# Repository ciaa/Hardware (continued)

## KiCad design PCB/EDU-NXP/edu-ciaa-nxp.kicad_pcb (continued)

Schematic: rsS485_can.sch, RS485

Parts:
C1: 10uF; c_1206_tantalio; Digikey 399-3525-1-ND
C2: 100nF; c_0805; Digikey 399-1167-1-ND
D1, D2, D3: PSD12C; DO-214AA(SMB); Digikey P6SMB12CAT3GOSCT-ND
J1: TB_1X3; bornier3; Digikey ED2610-ND
JP1, JP2, JP3, JP4: JUMPER-2
PS1, PS2: USMF020; SM1210; Digikey MF-USMF020-2CT-ND
R1, R2, R3: 4K7; SM0805; Digikey 1276-5544-1-ND
R4, R5: 100K; SM0805; Digikey P100KACT-ND
R6, R8: 390; SM0805; Digikey RR12P390DCT-ND
R7: 200; SM0805; Digikey RR12P200DCT-ND
R9: 100; SM0805; Digikey P16057CT-ND
U1: SN65HVD1176DR; -SOIC8; Digikey 296-26337-1-ND

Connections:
+5V: C1.2, C2.1 (A), R4.1 (A), R6.1 (A), U1.8 (VCC); also elsewhere on the board
/CPU/RS485_DIR: JP1.1, R3.1 (A), U1.3 (DE); also elsewhere on the board
/CPU/RS485_RXD: R1.2 (B), U1.1 (RO); also elsewhere on the board
/CPU/RS485_TXD: U1.4 (DI); also elsewhere on the board
GND: C1.1 (GND), C2.2 (B), D1.1 (cathode), D3.2 (Anode), R2.2 (B), R3.2 (B), R5.2 (B), R8.2 (B), R9.1 (A), U1.5 (GND); also elsewhere on the board
unnamed: J1.3, R9.2 (B)
unnamed: JP4.1, R8.1 (A)
unnamed: JP3.1, R7.1 (A)
unnamed: J1.2, PS2.2
unnamed: J1.1, PS1.2
unnamed: JP2.2, R6.2 (B)
unnamed: JP1.2, R2.1 (A), U1.2 (~RE~)
unnamed: D1.2 (Anode), D2.1 (cathode), JP2.1, JP3.2, PS1.1, R4.2 (B), U1.6 (A)
unnamed: D2.2 (Anode), D3.1 (cathode), JP4.2, PS2.1, R5.1 (A), R7.2 (B), U1.7 (B)

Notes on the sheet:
RS485
JP2, JP3, JP4: cortocircuitar en caso que sea el último nodo de la red.
Los resistores de 290 y 200 (220 valor E12/E24) se denominas bias resistors y son los recomendados la especificación de Profibus.
R9 de acuerdo a Fig 27 de la AN: slla070d de TI.

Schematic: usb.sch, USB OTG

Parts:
C3: 10uF; c_1206_tantalio; Digikey 399-3525-1-ND
C4, C50: 100nF; c_0805; Digikey 399-1167-1-ND
FB1: MI0805M221R-10; SM0805; Digikey 240-2392-1-ND
FB2: HZ0805E601R-10; SM0805; Digikey 240-2399-1-ND
J2: ZX62D-AB-5P8; USB_microAB_ZX62-AB-5P8; Digikey H11494CT-ND
R16, R17: 10k; SM0805; Digikey P10KACT-ND
TR1: DLW21HN900SQ2; SRF2012; Digikey 490-1064-2-ND
U2: PRTR5V0U2X; sot143B; Digikey 568-4140-1-ND
U9: MIC2025; -SOIC8; Digikey 576-1058-ND

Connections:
+5V: C50.1, U9.7; also elsewhere on the board
/CPU/USB_DM: TR1.3, U2.2 (I/O); also elsewhere on the board
/CPU/USB_DP: TR1.2, U2.3 (I/O); also elsewhere on the board
/CPU/USB_ID: J2.4; also elsewhere on the board
/CPU/USB_PPWR: R17.2, U9.1; also elsewhere on the board
/CPU/USB_PWR_FAULT: R16.1, U9.2; also elsewhere on the board
/CPU/USB_VBUS: C3.1, C4.1, FB1.2, U2.4 (VCC), U9.6, U9.8; also elsewhere on the board
/USB_OTG/CHJ2: FB2.2, J2.6, J2.7, J2.8, J2.9, U2.1 (GND)
GND: C3.2, C4.2, C50.2, FB2.1, J2.5, R17.1, U9.3; also elsewhere on the board
unnamed: FB1.1, J2.1
unnamed: J2.2, TR1.4
unnamed: J2.3, TR1.1

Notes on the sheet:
USB OTG
POWER SWITCH
ESD PROTECTION
Par diferencial 90 Ohm

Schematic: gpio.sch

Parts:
P1, P2: CONN_20X2
R20: 470; SM0805; Digikey P470ACT-ND
R21, R22, R23: 1k2; SM0805; Digikey RMCF0805JT1K20CT-ND
TH1, TH2, TH3, TH4: MF-MSMF030-2; MF-MSMF; Digikey MF-MSMF030-2CT-ND

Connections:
+3.3VADC: P1.17; also elsewhere on the board
+5V: TH2.2, TH4.2; also elsewhere on the board
/CPU/ADC0_1: R21.1; also elsewhere on the board
/CPU/ADC0_2: R22.1; also elsewhere on the board
/CPU/ADC0_3: R23.1; also elsewhere on the board
/CPU/CAN_RD: P1.27; also elsewhere on the board
/CPU/CAN_TD: P1.29; also elsewhere on the board
/CPU/DAC: R20.1; also elsewhere on the board
/CPU/ENET_CRS_DV: P2.10; also elsewhere on the board
/CPU/ENET_MDC: P2.8; also elsewhere on the board
/CPU/ENET_MDIO: P2.12; also elsewhere on the board
/CPU/ENET_REF_CLK: P2.15; also elsewhere on the board
/CPU/ENET_RXD0: P2.9; also elsewhere on the board
/CPU/ENET_RXD1: P2.4; also elsewhere on the board
/CPU/ENET_TXD0: P2.14; also elsewhere on the board
/CPU/ENET_TXD1: P2.16; also elsewhere on the board
/CPU/ENET_TX_EN: P2.6; also elsewhere on the board
/CPU/GPIO0: P2.29; also elsewhere on the board
/CPU/GPIO1: P2.32; also elsewhere on the board
/CPU/GPIO2: P2.31; also elsewhere on the board
/CPU/GPIO3: P2.34; also elsewhere on the board
/CPU/GPIO4: P2.33; also elsewhere on the board
/CPU/GPIO5: P2.36; also elsewhere on the board
/CPU/GPIO6: P2.35; also elsewhere on the board
/CPU/GPIO7: P2.38; also elsewhere on the board
/CPU/GPIO8: P2.40; also elsewhere on the board
/CPU/I2C_SCL: P1.21; also elsewhere on the board
/CPU/I2C_SDA: P1.19; also elsewhere on the board
/CPU/ISP: P1.5; also elsewhere on the board
/CPU/LCD1: P2.30; also elsewhere on the board
/CPU/LCD2: P2.28; also elsewhere on the board
/CPU/LCD3: P2.26; also elsewhere on the board
/CPU/LCD4: P2.22; also elsewhere on the board
/CPU/LCD_RS: P2.24; also elsewhere on the board
/CPU/RESET: P1.3; also elsewhere on the board
/CPU/RS232_RXD: P1.23; also elsewhere on the board
/CPU/RS232_TXD: P1.25; also elsewhere on the board
/CPU/SPI_MISO: P2.18; also elsewhere on the board
/CPU/SPI_MOSI: P2.21; also elsewhere on the board
/CPU/SPI_SCK: P2.20; also elsewhere on the board
/CPU/TEC_COL0: P1.39; also elsewhere on the board
/CPU/TEC_COL1: P1.31; also elsewhere on the board
/CPU/TEC_COL2: P1.34; also elsewhere on the board
/CPU/TEC_F0: P1.33; also elsewhere on the board
/CPU/TEC_F1: P1.36; also elsewhere on the board
/CPU/TEC_F2: P1.37; also elsewhere on the board
/CPU/TEC_F3: P1.35; also elsewhere on the board
/GPIO/LCD_EN: P2.23; also elsewhere on the board
/GPIO/WAKEUP: P1.6; also elsewhere on the board
GND: P1.4, P1.20, P1.22, P1.24, P1.26, P1.28, P1.30, P1.32, P1.38, P1.40, P2.3, P2.5, P2.7, P2.11, P2.13, P2.17, P2.19, P2.25, P2.27, P2.37, P2.39; also elsewhere on the board
GNDA: P1.7, P1.8, P1.10, P1.12, P1.14, P1.16, P1.18; also elsewhere on the board
unnamed: P1.1, TH1.1
unnamed: P1.2, TH2.1
unnamed: P1.15, R20.2
unnamed: P1.13, R21.2
unnamed: P1.11, R22.2
unnamed: P1.9, R23.2
unnamed: P2.2, TH4.1
unnamed: P2.1, TH3.1

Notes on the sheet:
Conectores de expansión LVTTL. En formato de pines, 2.54mm de pitch.
GPIO

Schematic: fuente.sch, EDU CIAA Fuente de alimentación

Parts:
C5, C6: 10uF; c_1206_tantalio; Digikey 399-3684-2-ND
C49: 100nF; c_0805; Digikey 399-1167-1-ND
D4, D5, D10: PMEG3020EH; DO-214AA(SMB); Digikey 568-4129-1-ND
D6: LED red; LED-0805; Digikey 1080-1412-1-ND
FB3, FB4: HZ0805E601R-10; SM0805; Digikey 240-2399-1-ND
P4: WM4200-ND; Con_2P; Digikey WM4200-ND
R57: 1k; SM0805; Digikey 311-1.0KARCT-ND
U3: NCP1117ST33T3G; SOT223; Digikey NCP1117ST33T3GOSCT-ND
ZA1: SMAZ5V6; SOD123F; Digikey MMSZ5V6T1GOSCT-ND

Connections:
+3.3VADC: FB3.2; also elsewhere on the board
+5V: C5.1, C49.1, D4.2 (K), D5.2 (K), D10.2 (K), R57.1, U3.3 (VI), ZA1.2 (K); also elsewhere on the board
/CPU/USB_DEBUG_VBUS: D5.1 (A); also elsewhere on the board
/CPU/USB_VBUS: D4.1 (A); also elsewhere on the board
GND: C5.2, C6.2, C49.2, D6.2 (K), FB4.1, P4.1, U3.1 (GND), ZA1.1 (A); also elsewhere on the board
GNDA: FB4.2; also elsewhere on the board
unnamed: D10.1 (A), P4.2
unnamed: D6.1 (A), R57.2

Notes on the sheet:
Fuente de alimentación a través de los puertos USB o de la entrada de 5V Tensiones de salida: 5V y 3.3V

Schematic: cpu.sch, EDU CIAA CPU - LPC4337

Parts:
BT1: BK-913; BK-913-ND; Digikey BK-913-ND
C11, C12, C13, C14, C15, C16: 20p; c_0805; Digikey 399-8033-1-ND
C17, C18, C19, C20, C21, C22, C23, C24, C25, C26, C27, C28, C29, C30, C31, C32, C34, C36, C38, C40, C41, C42, C43, C44, C45, C46, C47, C48, C51: 100nF; c_0805; Digikey 399-1167-1-ND
C33, C37, C39: 10uF; c_1206_tantalio; Digikey 399-3525-1-ND
C35: 3.3uF; c_0805; Digikey 445-7582-1-ND
D11: LL4148; SOD-80; Digikey LL4148FSTR-ND
FB5, FB6, FB9, FB10: MI0805M221R-10; SM0805; Digikey 240-2392-1-ND
FB7, FB8: HZ0805E601R-10; SM0805; Digikey 240-2399-1-ND
J3: ZX62D-AB-5P8; USB_microAB_ZX62-AB-5P8; Digikey H11494CT-ND
JP5: ISP
P3: Cortex-Debug; Pin_Array_5x2_1.27mm_SMD; Digikey FTSH-105-01-L-DV-K-TR-ND
R11, R15, R107, R108, R109, R110: 0; SM0805; Digikey 311-0.0ARCT-ND
R90: 100K; SM0805; Digikey P100KACT-ND
R91: 10M; SM0805; Digikey RMCF0805JT10M0CT-ND
R92: 12K; SM0805; Digikey 311-12.0KCRCT-ND
R93, R94, R99, R100, R102: 10K; SM0805; Digikey P10KACT-ND
R95, R97: 2.2k; SM0805; Digikey RMCF0805JT2K20CT-ND
R96, R98: 15K; SM0805; Digikey RR12P15.0KDCT-ND
R101: 2.2K; SM0805; Digikey RMCF0805JT2K20CT-ND
R103: 12K 1%; SM0805; Digikey 311-12.0KCRCT-ND
R104: 1k; SM0805; Digikey RR12P15.0KDCT-ND
R105: 270; SM0805; Digikey RHM270CPCT-ND
R106: 10k; SM0805; Digikey P10KACT-ND
SW5: RESET; PUSH_SWITCH_THT; Digikey 450-1804-ND
TR2: DLW21HN900SQ2; SRF2012; Digikey 490-1064-2-ND
U4: LPC4337JBD144; LQFP144-M05; Digikey 568-10159-ND
U5: 93C46; -SOIC8; Digikey AT93C46DN-SH-TCT-ND
U6: FT2232H; LQFP64-M05; Digikey 768-1024-1-ND
U7: TXB0108; tssop-20; Digikey 296-21527-1-ND
U8: PRTR5V0U2X; sot143B; Digikey 568-4140-1-ND
X1: 32.768K; 4SOJ; Digikey 535-9166-1-ND
X2, X3: 12MHz; FA238V-XTAL; Digikey 887-1831-1-ND

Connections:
+3.3VADC: C18.1, C19.1, C32.1, C33.2, FB10.2, U4.137 (VDDA); also elsewhere on the board
/CPU/ADC0_1: U4.2 (ADC0_1/ADC1_1); also elsewhere on the board
/CPU/ADC0_2: U4.143 (ADC0_2/ADC1_2); also elsewhere on the board
/CPU/ADC0_3: U4.139 (ADC0_3/ADC1_3); also elsewhere on the board
/CPU/CAN_RD: U4.114 (P3_1); also elsewhere on the board
/CPU/CAN_TD: U4.116 (P3_2); also elsewhere on the board
/CPU/CHJ3: FB5.1, J3.6, J3.7, J3.8, J3.9, U8.1 (GND)
/CPU/DAC: U4.6 (ADC0_0/ADC1_0/DAC); also elsewhere on the board
/CPU/EECLK: R100.2, U5.2 (SK), U6.62 (EECLK)
/CPU/EECS: R102.2, U5.1 (CS), U6.63 (EECS)
/CPU/EEDATA: R101.1, U5.3 (DI), U6.61 (EEDATA)
/CPU/ENET_CRS_DV: U4.64 (P1_16); also elsewhere on the board
/CPU/ENET_MDC: U4.140 (P7_7); also elsewhere on the board
/CPU/ENET_MDIO: U4.66 (P1_17); also elsewhere on the board
/CPU/ENET_REF_CLK: U4.68 (P1_19); also elsewhere on the board
/CPU/ENET_RXD0: U4.62 (P1_15); also elsewhere on the board
/CPU/ENET_RXD1: U4.32 (P0_0); also elsewhere on the board
/CPU/ENET_TXD0: U4.67 (P1_18); also elsewhere on the board
/CPU/ENET_TXD1: U4.70 (P1_20); also elsewhere on the board
/CPU/ENET_TX_EN: U4.34 (P0_1); also elsewhere on the board
/CPU/FT_OE: R105.2, U6.28 (ACBUS2)
/CPU/FT_RST: U6.27 (ACBUS1), U7.7 (A6)
/CPU/FT_TCK: U6.16 (ADBUS0), U7.1 (A1)
/CPU/FT_TDI: U6.17 (ADBUS1), U7.3 (A2)
/CPU/FT_TDO: U6.18 (ADBUS2), U7.4 (A3)
/CPU/FT_TMS: U6.19 (ADBUS3), U7.5 (A4)
/CPU/FT_TRST: U6.26 (ACBUS0), U7.6 (A5)
/CPU/FT_XTIN: C15.2, U6.2 (OSCI), X3.3
/CPU/FT_XTOUT: C16.2, U6.3 (OSCO), X3.1
/CPU/GPIO0: U4.74 (P6_1); also elsewhere on the board
/CPU/GPIO1: U4.80 (P6_4); also elsewhere on the board
/CPU/GPIO2: U4.82 (P6_5); also elsewhere on the board
/CPU/GPIO3: U4.85 (P6_7); also elsewhere on the board
/CPU/GPIO4: U4.86 (P6_8); also elsewhere on the board
/CPU/GPIO5: U4.97 (P6_9); also elsewhere on the board
/CPU/GPIO6: U4.100 (P6_10); also elsewhere on the board
/CPU/GPIO7: U4.101 (P6_11); also elsewhere on the board
/CPU/GPIO8: U4.103 (P6_12); also elsewhere on the board
/CPU/I2C_SCL: R95.2, U4.92 (I2C0_SCL); also elsewhere on the board
/CPU/I2C_SDA: R97.2, U4.93 (I2C0_SDA); also elsewhere on the board
/CPU/ISP: U4.134 (P7_6); also elsewhere on the board
/CPU/LCD1: U4.9 (P4_4); also elsewhere on the board
/CPU/LCD2: U4.10 (P4_5); also elsewhere on the board
/CPU/LCD3: U4.11 (P4_6); also elsewhere on the board
/CPU/LCD4: U4.35 (P4_10); also elsewhere on the board
/CPU/LCD_RS: U4.15 (P4_8); also elsewhere on the board
/CPU/LED0_B: U4.84 (P2_2); also elsewhere on the board
/CPU/LED0_G: U4.81 (P2_1); also elsewhere on the board
/CPU/LED0_R: U4.75 (P2_0); also elsewhere on the board
/CPU/LED1: U4.104 (P2_10); also elsewhere on the board
/CPU/LED2: U4.105 (P2_11); also elsewhere on the board
/CPU/LED3: U4.106 (P2_12); also elsewhere on the board
/CPU/PULS_0: U4.38 (P1_0); also elsewhere on the board
/CPU/PULS_1: U4.42 (P1_1); also elsewhere on the board
/CPU/PULS_2: U4.43 (P1_2); also elsewhere on the board
/CPU/PULS_3: U4.49 (P1_6); also elsewhere on the board
/CPU/RESET: D11.2, P3.10, R15.1; also elsewhere on the board
/CPU/RS232_RXD: U4.88 (P2_4); also elsewhere on the board
/CPU/RS232_TXD: U4.87 (P2_3); also elsewhere on the board
/CPU/RS485_DIR: U4.78 (P6_2); also elsewhere on the board
/CPU/RS485_RXD: U4.72 (P9_6); also elsewhere on the board
/CPU/RS485_TXD: U4.69 (P9_5); also elsewhere on the board
/CPU/RST: R15.2, U7.14 (B6)
/CPU/RTCX1: C11.2, U4.125 (RTCX1), X1.4
/CPU/RTCX2: C12.2, U4.126 (RTCX2), X1.1
/CPU/SPI_MISO: U4.44 (P1_3); also elsewhere on the board
/CPU/SPI_MOSI: U4.47 (P1_4); also elsewhere on the board
/CPU/SPI_SCK: U4.120 (PF_4); also elsewhere on the board
/CPU/TCK: P3.4, U4.27 (TCK/SWDCLK), U7.20 (B1)
/CPU/TDI: P3.8, U4.26 (TDI), U7.18 (B2)
/CPU/TDO: P3.6, U4.31 (TDO/SWO), U7.17 (B3)
/CPU/TEC_COL0: U4.48 (P1_5); also elsewhere on the board
/CPU/TEC_COL1: U4.132 (P7_4); also elsewhere on the board
/CPU/TEC_COL2: U4.133 (P7_5); also elsewhere on the board
/CPU/TEC_F0: U4.1 (P4_0); also elsewhere on the board
/CPU/TEC_F1: U4.3 (P4_1); also elsewhere on the board
/CPU/TEC_F2: U4.8 (P4_2); also elsewhere on the board
/CPU/TEC_F3: U4.7 (P4_3); also elsewhere on the board
/CPU/TMS: P3.2, U4.30 (TMS/SWDIO), U7.16 (B4)
/CPU/TRST: R11.2, U7.15 (B5)
/CPU/U2_RXD: U4.115 (P7_2), U6.38 (BDBUS0)
/CPU/U2_TXD: U4.113 (P7_1), U6.39 (BDBUS1)
/CPU/USB_DEBUG_VBUS: FB6.2; also elsewhere on the board
/CPU/USB_DM: R98.1, U4.20 (USB0_DM); also elsewhere on the board
/CPU/USB_DP: R96.1, U4.18 (USB0_DP); also elsewhere on the board
/CPU/USB_ID: U4.22 (USB0_ID); also elsewhere on the board
/CPU/USB_JTAG_1.8V: C35.1, C41.1, C42.1, C43.1, U6.12 (VCORE), U6.37 (VCORE), U6.49 (VREGOUT), U6.64 (VCORE)
/CPU/USB_JTAG_DM: TR2.3, U6.7 (DM), U8.3 (I/O)
/CPU/USB_JTAG_DP: TR2.2, U6.8 (DP), U8.2 (I/O)
/CPU/USB_PPWR: U4.79 (P6_3); also elsewhere on the board
/CPU/USB_PWR_FAULT: U4.83 (P6_6); also elsewhere on the board
/CPU/USB_VBUS: U4.21 (USB0_VBUS); also elsewhere on the board
/CPU/XTAL1: C14.2, R91.1, U4.12 (XTAL1), X2.1
/CPU/XTAL2: C13.2, R91.2, U4.13 (XTAL2), X2.3
/CPU/nTRST: R11.1, R94.1, U4.29 (nTRST)
/GPIO/LCD_EN: U4.33 (P4_9); also elsewhere on the board
/GPIO/WAKEUP: U4.130 (WAKEUP0); also elsewhere on the board
GND: BT1.2 (-), C11.1, C12.1, C13.1, C14.1, C15.1, C16.1, C17.2, C20.1, C21.1, C22.1, C23.1, C24.1, C25.1, C26.1, C27.1, C28.1, C29.1, C30.1, C31.1, C34.2, C35.2, C36.2, C37.2, C38.2, C39.2, C40.1, C41.2, C42.2, C43.2, C44.2, C45.2, C46.2, C47.2, C48.1, C51.2, FB5.2, FB9.1, J3.4, J3.5, JP5.1, P3.3, P3.5, P3.9, R92.2, R96.2, R98.2, R103.1, R106.2, R107.1, R108.1, R109.1, R110.1, SW5.3, SW5.4, U4.4 (VSSIO), U4.40 (VSSIO), U4.76 (VSSIO), U4.109 (VSSIO), U5.5 (GND), U5.7 (NC), U6.1 (GND), U6.5 (GND), U6.10 (AGND), U6.11 (GND), U6.13 (TEST), U6.15 (GND), U6.25 (GND), U6.35 (GND), U6.47 (GND), U6.51 (GND), U7.11 (GND), X2.2, X2.4, X3.2, X3.4; also elsewhere on the board
GNDA: C18.2, C19.2, C32.2, C33.1, U4.135 (VSSA); also elsewhere on the board
unnamed: JP5.2, U4.96 (P2_7)
unnamed: J3.3, TR2.1
unnamed: J3.2, TR2.4
unnamed: C38.1, C39.1, FB8.1, U6.9 (VPLL)
unnamed: R103.2, U6.6 (REF)
unnamed: R104.2, U6.14 (~RESET)
unnamed: R99.2, R101.2, U5.4 (DO)
unnamed: R107.2, U7.8 (A7)
unnamed: C36.1, C37.1, FB7.1, U6.4 (VPHY)
unnamed: R110.2, U7.13 (B7)
unnamed: R109.2, U7.12 (B8)
unnamed: R105.1, R106.1, U7.10 (OE)
unnamed: R108.2, U7.9 (A8)
unnamed: FB9.2, U4.19 (USB0_VSSA_TERM), U4.23 (USB0_VSSA_REF)
unnamed: BT1.1 (+), C51.1, U4.127 (VBAT)
unnamed: FB10.1, U4.16 (USB0_VDDA_3V3_DRIVER), U4.17 (USB0_VDDA3V3)
unnamed: FB6.1, J3.1, U8.4 (VCC)
unnamed: R92.1, U4.24 (USB0_RREF)
unnamed: R93.1, U4.28 (DBGEN)
unnamed: C17.1, D11.1, R90.1, SW5.1, SW5.2, U4.128 (nRESET)

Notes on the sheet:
Microcontrolador NXP LPC4337 con memoria EEPROM, batería RTC y debugger basado en FT2232.
Bat. CR2032

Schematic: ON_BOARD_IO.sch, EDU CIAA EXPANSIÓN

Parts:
C7, C8, C9, C10: 100nF; c_0805; Digikey 399-1167-1-ND
D7: LED; LED-0805; Digikey 1080-1412-1-ND
D8: LED; LED-0805; Digikey 1080-1410-1-ND
D9: LED; LED-0805; Digikey 1080-1411-1-ND
LED1: LED_ARBG; PLCC-4; Digikey 160-2022-1-ND
Q1, Q3, Q4, Q5, Q9, Q10: 2N7002; SOT23GDS; Digikey 2N7002NCT-ND
R10, R12, R13, R14, R18, R19: 330k; SM0805; Digikey RMCF0805JT330KCT-ND
R58, R59, R60, R61: 1k; SM0805; Digikey 311-1.0KARCT-ND
R62, R63, R64, R65, R66, R70, R71, R74, R82, R83: 10k; SM0805; Digikey P10KACT-ND
R68, R72, R73, R76, R84, R85: 680; SM0805; Digikey RR12P680DCT-ND
SW1: TEC_1; PUSH_SWITCH_THT; Digikey 450-1804-ND
SW2: TEC_2; PUSH_SWITCH_THT; Digikey 450-1804-ND
SW3: TEC_3; PUSH_SWITCH_THT; Digikey 450-1804-ND
SW4: TEC_4; PUSH_SWITCH_THT; Digikey 450-1804-ND

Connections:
+5V: D7.1 (A), D8.1 (A), D9.1 (A), LED1.4 (A); also elsewhere on the board
/CPU/LED0_B: R10.1, R66.1; also elsewhere on the board
/CPU/LED0_G: R12.1, R70.1; also elsewhere on the board
/CPU/LED0_R: R14.1, R74.1; also elsewhere on the board
/CPU/LED1: R18.1, R82.1; also elsewhere on the board
/CPU/LED2: R13.1, R71.1; also elsewhere on the board
/CPU/LED3: R19.1, R83.1; also elsewhere on the board
/CPU/PULS_0: R58.1; also elsewhere on the board
/CPU/PULS_1: R59.1; also elsewhere on the board
/CPU/PULS_2: R60.1; also elsewhere on the board
/CPU/PULS_3: R61.1; also elsewhere on the board
GND: C7.2, C8.2, C9.2, C10.2, Q1.S, Q3.S, Q4.S, Q5.S, Q9.S, Q10.S, R10.2, R12.2, R13.2, R14.2, R18.2, R19.2, SW1.3, SW1.4, SW2.3, SW2.4, SW3.3, SW3.4, SW4.3, SW4.4; also elsewhere on the board
unnamed: LED1.3 (G), R72.1
unnamed: D7.2 (K), R73.1
unnamed: Q4.G, R71.2
unnamed: Q4.D, R73.2
unnamed: Q5.G, R74.2
unnamed: LED1.2 (R), R76.1
unnamed: Q3.G, R70.2
unnamed: Q3.D, R72.2
unnamed: Q5.D, R76.2
unnamed: Q10.G, R83.2
unnamed: Q10.D, R85.2
unnamed: D9.2 (K), R85.1
unnamed: D8.2 (K), R84.1
unnamed: C8.1, R59.2, R63.2, SW2.1, SW2.2
unnamed: C7.1, R58.2, R62.2, SW1.1, SW1.2
unnamed: Q9.G, R82.2
unnamed: Q9.D, R84.2
unnamed: Q1.G, R66.2
unnamed: LED1.1 (B), R68.1
unnamed: Q1.D, R68.2
unnamed: C9.1, R60.2, R64.2, SW3.1, SW3.2
unnamed: C10.1, R61.2, R65.2, SW4.1, SW4.2

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
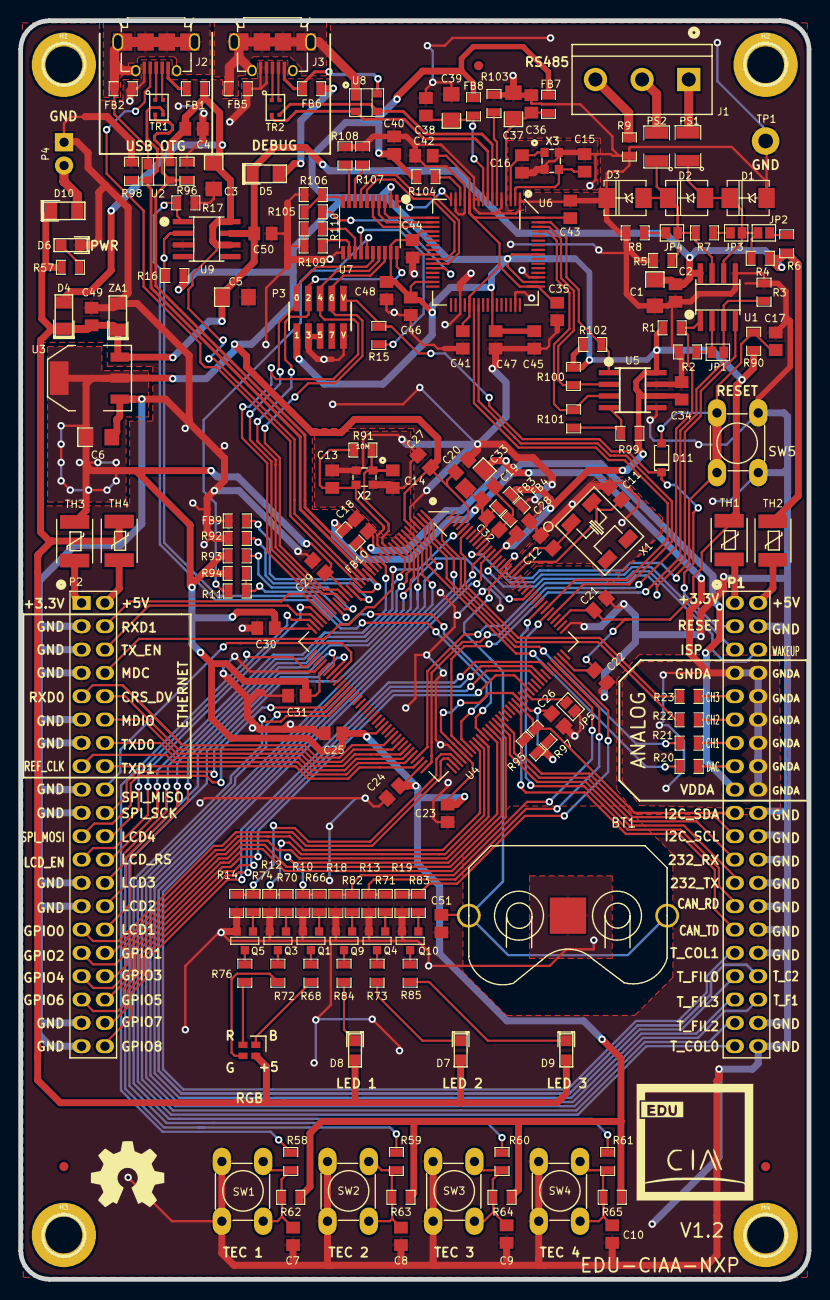
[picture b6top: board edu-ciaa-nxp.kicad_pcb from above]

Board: 2 copper layers, 85.8 x 137.0 mm, 195 parts (0 on the bottom side), 166 nets.

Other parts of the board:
G101: OSHWA

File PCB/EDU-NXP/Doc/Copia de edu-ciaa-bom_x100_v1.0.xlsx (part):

Componente | Cantidad por PCB | Referencia | Descripción | Código Digi-Key | Código Mouser | Cantidad para 100 PCBs | Costo unitario x100 (USD FOB DigiKey) | Costo por PCB x100 (USD FOB DigiKey) | Costo unitario x1000(USD FOB DigiKey) | Costo por PCB x1000 (USD FOB DigiKey)
BK-913 | 1 | BT1 | Soporte batería CR2032 | BK-913-ND | 534-3003 | 100 | 0.27 | 0.27 | 2.1999999999999999E-2 | 2.1999999999999999E-2
15pF | 2 | C11 C12 | Cap. Cerámico 0805 | 1276-1163-1-ND | 581-08055A150J | 200 | 2.1999999999999999E-2 | 4.3999999999999997E-2 | 1.2E-2 | 2.4E-2
20pF | 2 | C13 C14 | Cap. Cerámico 0805 | 399-8033-1-ND | 81-GQM2195C1H200JB01 | 200 | 0.1008 | 0.2016 | 6.1199999999999997E-2 | 0.12239999999999999
22pF | 2 | C15 C16 | Cap. Cerámico 0805 | 399-1113-1-ND | 80-C0805C220J5G | 200 | 2.24E-2 | 4.48E-2 | 1.2E-2 | 2.4E-2
100nF | 34 | C2 C4 C7 C8 C9 C10 C17 C18 C19 C20 C21 C22 C23 C24 C25 C26 C27 C28 C29 C30 C31 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 | Cap. Cerámico 0805 | 399-1167-1-ND | 581-08055C104J | 3400 | 3.56E-2 | 1.2103999999999999 | 2.0629999999999999E-2 | 0.70141999999999993
3.3uF | 1 | C35 | Cap. Cerámico 0805 | 445-7582-1-ND | 810-C2012X5R1H335K | 100 | 0.16070000000000001 | 0.16070000000000001 | 0.10349999999999999 | 0.10349999999999999
10uF | 6 | C1 C3 C6 C33 C37 C39 | Cap. Cerámico 1206 | 399-3525-1-ND | 81-GRM31CR71C106KAC7 | 600 | 0.17499999999999999 | 1.0499999999999998 | 0.115 | 0.69000000000000006
330uF | 1 | C5 | Cap. Aluminio SMD | 493-9422-1-ND | 647-UCW1E331MNL1GS | 100 | 0.40610000000000002 | 0.40610000000000002 | 0.34060000000000001 | 0.34060000000000001
PSD12C | 3 | D1 D2 D3 | TVS | P6SMB12CAT3GOSCT-ND | 863-P6SMB12CAT3G | 300 | 0.28770000000000001 | 0.86309999999999998 | 0.14745 | 0.44235000000000002
PMEG3020EH | 2 | D4 D5 | Diodo Schottky | 568-4129-1-ND | 771-PMEG3020EH-T/R | 200 | 0.2505 | 0.501 | 0.12839 | 0.25678000000000001
LED | 4 | D6 D7 D8 D9 | LED Rojo 0805 | 1080-1412-1-ND | 78-VLMS1300-GS08 | 400 | 0.2112 | 0.8448 | 0.1152 | 0.46079999999999999
BLM18KG221SN1 | 3 | FB1 FB5 FB6 | EMI Filter 0603 | 490-5255-1-ND | 81-BLM18KG221SN1D | 300 | 5.2299999999999999E-2 | 0.15689999999999998 | 3.0099999999999998E-2 | 9.0299999999999991E-2
HZ0805E601R-10 | 5 | FB2 FB3 FB4 FB7 FB8 | EMI Filter 0805 | 240-2399-1-ND | 875-HZ0805E601R-10 | 500 | 3.8100000000000002E-2 | 0.1905 | 2.1950000000000001E-2 | 0.10975
TB_1X3 | 1 | J1 | Bornes fijos x3 | ED2610-ND | 571-7969493 | 100 | 0.36799999999999999 | 0.36799999999999999 | 0.26400000000000001 | 0.26400000000000001
ZX62-AB-5PA | 2 | J2 J3 | Conector micro USB tipo AB | H11635CT-ND | 798-ZX62-AB-5PA11 | 200 | 0.77439999999999998 | 1.5488 | 0.56320000000000003 | 1.1264000000000001
LED RGB | 1 | LED1 | led RGB SDM | 160-2022-1-ND | 859-LTST-C19FD1WT | 100 | 0.29930000000000001 | 0.29930000000000001 | 0.17100000000000001 | 0.17100000000000001
Pines 2x20 | 2 | P1 P2 | Tira de pines 2x20 | S6104-ND |  | 200 | 1.6938 | 3.3875999999999999 | 1.25153 | 2.5030600000000001
Conector IDE | 1 | P3 | Conector 2x5 1.27mm SMD para DEBUG | 952-1389-ND | 855-M50-3600542 | 100 | 0.88 | 0.88 | 0.64 | 0.64
USMF020 | 2 | PS1 PS2 | Polyswitch | MF-USMF020-2CT-ND | 652-MF-USMF020-2 | 200 | 0.22639999999999999 | 0.45279999999999998 |  | 0
2N7002 | 12 | Q1 Q2 Q3 Q4 Q5 Q6 Q7 Q8 Q9 Q10 Q11 Q12 | Mosfet canal N SOT23 | 2N7002NCT-ND | 512-2N7002 | 1200 | 0.1363 | 1.6356000000000002 | 4.5420000000000002E-2 | 0.54503999999999997
0 | 4 | R107 R108 R109 R110 | Resistor SMD 0805 | 311-0.0ARCT-ND | 667-ERJ-6GEY0R00V | 400 | 7.3000000000000001E-3 | 2.92E-2 | 3.2599999999999999E-3 | 1.304E-2
4K7 | 3 | R1 R2 R3 | Resistor SMD 0805 | 1276-5544-1-ND | 667-ERJ-S06J472V | 300 | 7.1000000000000004E-3 | 2.1299999999999999E-2 | 3.2100000000000002E-3 | 9.6299999999999997E-3
100K | 2 | R4 R5 | Resistor SMD 0805 | RR12P100KDCT-ND | 667-ERJ-6GEYJ104V | 200 | 1.49E-2 | 2.98E-2 | 5.4400000000000004E-3 | 1.0880000000000001E-2
680 | 8 | R6 R8 R68 R72 R73 R76 R84 R85 | Resistor SMD 0805 | RR12P680DCT-ND | 754-RR1220P-681D | 800 | 7.3000000000000001E-3 | 5.8400000000000001E-2 | 3.2599999999999999E-3 | 2.6079999999999999E-2
120 | 1 | R7 | Resistor SMD 0805 | RR12P120DCT-ND | 667-ERJ-6GEYJ121V | 100 | 1.49E-2 | 1.49E-2 | 5.4400000000000004E-3 | 5.4400000000000004E-3
100 1/2W | 1 | R9 | Resistor SMD 0805 1/2W | P16057CT-ND | 667-ERJ-P06J101V | 100 | 6.6500000000000004E-2 | 6.6500000000000004E-2 | 2.4320000000000001E-2 | 2.4320000000000001E-2
330K | 6 | R10 R11 R12 R13 R14 R15 R16 R17 R18 R19 | Resistor SMD 0805 | RMCF0805JT330KCT-ND | 667-ERJ-6GEYJ334V | 600 | 8.8000000000000005E-3 | 5.28E-2 | 3.2000000000000002E-3 | 1.9200000000000002E-2
470 | 1 | R20 | Resistor SMD 0806 | P470ACT-ND | 603-AC0805JR-07470RL | 100 | 1.49E-2 | 1.49E-2 | 5.4000000000000003E-3 | 5.4000000000000003E-3
1K2 | 3 | R21 R22 R23 | Resistor SMD 0807 | RMCF0805JT1K20CT-ND | 660-RK73B2ATTD122J | 300 | 8.8000000000000005E-3 | 2.64E-2 | 3.2000000000000002E-3 | 9.6000000000000009E-3
1K | 6 | R57 R58 R59 R60 R61 R104 | Resistor SMD 0805 | 311-1.0KARCT-ND | 667-ERJ-6GEYJ102V | 600 | 7.3000000000000001E-3 | 4.3799999999999999E-2 | 3.2599999999999999E-3 | 1.9560000000000001E-2
10K | 17 | R62 R63 R64 R65 R66 R70 R71 R74 R82 R83 R90 R93 R94 R99 R100 R102 R106 | Resistor SMD 0805 | P10KACT-ND | 667-ERJ-6GEYJ103V | 1700 | 1.49E-2 | 0.25330000000000003 | 5.4400000000000004E-3 | 9.2480000000000007E-2
10M | 1 | R91 | Resistor SMD 0805 | RMCF0805JT10M0CT-ND | 667-ERJ-6GEYJ106V | 100 | 8.8000000000000005E-3 | 8.8000000000000005E-3 | 3.2000000000000002E-3 | 3.2000000000000002E-3
12K | 1 | R92 R103 | Resistor SMD 0805 1% | 311-12.0KCRCT-ND | 667-ERJ-S06F1202V | 100 | 8.3999999999999995E-3 | 8.3999999999999995E-3 | 3.79E-3 | 3.79E-3
2K2 | 3 | R95 R97 R101 | Resistor SMD 0805 | RMCF0805JT2K20CT-ND | 660-RK73B2ATTDD222J | 300 | 8.8000000000000005E-3 | 2.64E-2 | 3.2000000000000002E-3 | 9.6000000000000009E-3
15K | 2 | R96 R98 | Resistor SMD 0805 | RR12P15.0KDCT-ND | 754-RR1220P-153D | 200 | 3.8100000000000002E-2 | 7.6200000000000004E-2 | 1.6729999999999998E-2 | 3.3459999999999997E-2
270 | 1 | R105 | Resistor SMD 0805 | RHM270CPCT-ND | 660-RK73B2ATTDD271J | 100 | 1.04E-2 | 1.04E-2 | 4.6600000000000001E-3 | 4.6600000000000001E-3
PULSADOR | 5 | TEC_1 TEC_2 TEC_3 RESET | Tact switch SPST | 450-1792-1-ND | 612-TL3301BF260QG | 500 | 0.21540000000000001 | 1.077 | 0.1943 | 0.97150000000000003
MF-MSMF030-2 | 1 | TH1 TH3 | Polyswitch 0.3A SMD | MF-MSMF030-2CT-ND | 652-MF-MSMF030-2 | 100 | 0.24260000000000001 | 0.24260000000000001 | 0.18690000000000001 | 0.18690000000000001
MF-MSMF110-2 | 2 | TH2 TH4 | Polyswitch 1.1A SMD | MF-USMF110-2CT-ND | 652-MF-MSMF110-2 | 200 | 0.22639999999999999 | 0.45279999999999998 | 0.15920000000000001 | 0.31840000000000002
DLW21HN900SQ2 | 2 | TR1 TR2 | Choke USB | SRF2012-900YCT-ND | 81-DLW21HN900SQ2L | 200 | 0.33600000000000002 | 0.67200000000000004 | 0.24640000000000001 | 0.49280000000000002
SN65HVD1176DR | 1 | U1 | Transceptor RS485 SOIC8 | 296-26337-1-ND | 595-SN65HVD1176DR | 100 | 3.1017000000000001 | 3.1017000000000001 | 2.1168 | 2.1168
PRTR5V0U2X | 1 | U2 | TVS para USB SOT143 | 568-4140-1-ND | 771-PRTR5V0U2X-T/R | 100 | 0.35780000000000001 | 0.35780000000000001 | 0.20265 | 0.20265
NCP1117ST33T3G | 1 | U3 | Regulador 3.3V SOT223 | NCP1117ST33T3GOSCT-ND | 863-NCP1117ST33T3G | 100 | 0.31269999999999998 | 0.31269999999999998 | 0.17710000000000001 | 0.17710000000000001
LPC4337JBD144 | 1 | U4 | Microcontrolador LQFP144 | 568-10159-ND | 771-LPC4337JBD144E | 100 | 11.05 | 11.05 | 8.6449999999999996 | 8.6449999999999996
93C46 | 1 | U5 | EEPROM SOIC8 | AT93C46DN-SH-TCT-ND | 579-93C46A-E/SN | 100 | 0.22950000000000001 | 0.22950000000000001 | 0.21708 | 0.21708
FT2232H | 1 | U6 | USB IC 64-LQFP | 768-1024-1-ND | 895-FT2232HL | 100 | 5.4 | 5.4 | 4.0599999999999996 | 4.0599999999999996
TXB0108 | 1 | U7 | Buffer bidireccional 20-TSSOP | 296-21527-1-ND | 595-TXB0108PWR | 100 | 1.6704000000000001 | 1.6704000000000001 | 0.9 | 0.9
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
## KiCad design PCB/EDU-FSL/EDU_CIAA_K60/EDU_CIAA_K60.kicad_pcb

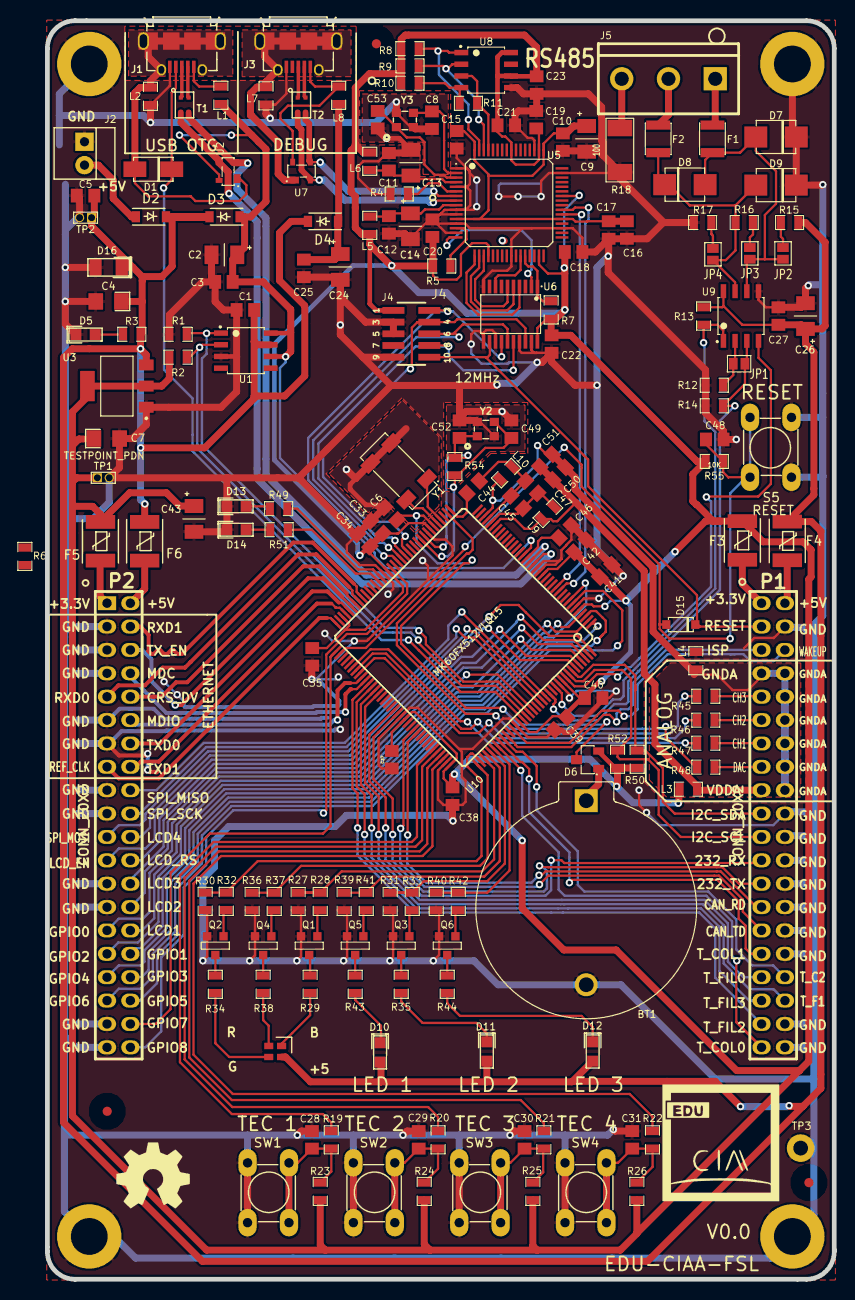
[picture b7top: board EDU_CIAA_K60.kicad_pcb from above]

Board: 2 copper layers, 85.5 x 136.8 mm, 187 parts (0 on the bottom side), 162 nets.

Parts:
BT1: CR2032; 2032batPTH
C1, C3, C5, C6, C10, C11, C12, C15, C16, C17, C18, C19, C20, C21, C22, C23, C25, C27, C28, C29, C30, C31, C33, C34, C35, C37, C38, C39, C40, C41, C42, C44, C45, C48, C50: 100nF; c_0805
C2: 4,7uF; c_1206POL
C4, C7: 10uF; c_1206_tantalio
C8, C49, C52, C53: 20pF; c_0805
C9, C13, C14, C24, C26, C43: 10uF; c_1206POL
C46: 2.2uF; c_0805
C47, C51: 10nF; c_0805
D1: SMAJ5.0A; DO-214AC_SMA
D2, D3, D4: PMEG3020EH; SOD-123
D5, D14: ST2; LED-0805
D6: BAT54C; SOT-23
D7, D8, D9: P6SMB12CAT3G; DO-214AA_SMB
D10, D11, D12: LED; LED-0805
D13: ST1; LED-0805
D15: LL4148; SOD-123
D16: SMAZ5V6; SOD123F
F1, F2: USMF020; ptc_1210
F3, F4, F5, F6: MF-MSMF030-2; MF-MSMF
FD1, FD2, FD3: FIDUCIAL; Fiducial_1mm
G1: LOGO
G2: OSHWA
J1, J3: ZX62D-AB-5P8; USB_microAB_ZX62-AB-5P8
J2: 0022232021; Con_2P
J4: FTSH-105-01-L-DV-K-TR; PIN_ARRAY_5x2_1.27_SMD
J5: TB_1X3; bornier3
JP1, JP2, JP3, JP4: JUMPER-2; GS2
L1, L7, L8, L9, L10: MI0805M221R-10; SM0805
L2, L3, L4, L5, L6: HZ0805E601R-10; SM0805
LED1: LED_ARBG; PLCC-4
MH1, MH2, MH3, MH4: PCB_HOLE
P1, P2: CONN_20X2; PIN_ARRAY_20X2
Q1, Q2, Q3, Q4, Q5, Q6: 2N7002; SOT23GDS
R1, R2: 10k; r_0805
R3: 1k; r_0805
R4: 12K 1%; r_0805
R5: 1K; r_0805
R6, R11, R50, R52: 2K2; r_0805
R7, R8, R9, R10, R55: 10K; r_0805
R12, R13, R14: 4K7; r_0805
R15, R17: 390; r_0805
R16: 220; r_0805
R18: 100; r_2010
R19, R20, R21, R22: 1k; SM0805
R23, R24, R25, R26, R28, R32, R33, R37, R41, R42: 10k; SM0805
R27, R30, R31, R36, R39, R40: 330k; SM0805
R29, R34, R35, R38, R43, R44: 680; SM0805
R45, R46, R47: 1k2; SM0805
R48: 470; SM0805
R49, R51: 680; r_0805
R54: 10M; r_0805
S5: RESET; PUSH_SWITCH_THT
SW1: TEC_1; PUSH_SWITCH_THT
SW2: TEC_2; PUSH_SWITCH_THT
SW3: TEC_3; PUSH_SWITCH_THT
SW4: TEC_4; PUSH_SWITCH_THT
T1, T2: DLW21HN900SQ2; SRF2012
TP1, TP2: TESTPOINT_PDN
TP3: 4mm
U1: MIC2025-2YM; SOIC-8
U2, U7: PRTR5V0U2X; SOT-143-4
U3: NCP1117ST33T3G; SOT-223
U5: FT2232H; TQFP64
U6: 74HC244; TSSOP-20
U8: 93C46; SOIC-8
U9: SN65HVD1176DR; SOIC-8
U10: MK60FX512VLQ15; LQFP144
Y1: 32.768KHZ; 4SOJ
Y2, Y3: 12MHz; FA238V-XTAL

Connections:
+3.3V: C7.1, C18.1, C19.1, C20.1, C21.1, C22.1, C23.1, C33.1, C34.1, C35.1, C37.1, C38.1, C39.1, C40.1, C41.1, C42.1, C43.1, D6.2, F3.2, F5.2, J4.1, L3.1, L5.1, L6.1, R2.1, R5.1, R6.1, R7.2, R8.1, R9.1, R10.1, R23.1, R24.1, R25.1, R26.1, R50.1, R52.1, R55.1, TP1.1, U3.2, U5.20, U5.31, U5.42, U5.50, U5.56, U6.20, U8.6, U8.8, U10.5, U10.16, U10.43, U10.56, U10.70, U10.94, U10.108, U10.122, U10.135
+3.3VADC: C50.1, C51.2, L3.2, L9.2, P1.17, U10.31
+5V: C1.1, C4.1, C5.1, C26.1, C27.2, D2.1, D3.1, D4.1, D10.1, D11.1, D12.1, D16.2, F4.2, F6.2, LED1.4, R3.1, R13.1, R15.1, TP2.1, U1.7, U3.3, U9.8
+USB_JTAG_1V8: C9.1, C10.1, C15.1, C16.1, C17.1, U5.12, U5.37, U5.49, U5.64
/CPU/AUX_UART_CTS/SPI_CLK: P2.20, U10.128
/CPU/AUX_UART_RX/SPI_MISO: P2.18, U10.130
/CPU/AUX_UART_TX/SPI_MOSI: P2.21, U10.129
/CPU/CAN_RD: P1.27, U10.98
/CPU/CAN_TD: P1.29, U10.97
/CPU/GPIO9: P1.5, U10.118
/CPU/I2C_SCL: P1.21, R52.2, U10.137
/CPU/I2C_SDA: P1.19, R50.2, U10.138
/CPU/LED0_B: R27.1, R28.1, U10.111
/CPU/LED0_G: R30.1, R32.1, U10.110
/CPU/LED0_R: R36.1, R37.1, U10.109
/CPU/LED1: R39.1, R41.1, U10.112
/CPU/LED2: R31.1, R33.1, U10.113
/CPU/LED3: R40.1, R42.1, U10.114
/CPU/PULS_0: R19.1, U10.103
/CPU/PULS_1: R20.1, U10.104
/CPU/PULS_2: R21.1, U10.105
/CPU/PULS_3: R22.1, U10.106
/CPU/RESET: D15.2, J4.10, P1.3, U6.12
/CPU/RS232_RXD: P1.23, U10.91
/CPU/RS232_TXD: P1.25, U10.92
/CPU/RS485_DIR: JP1.2, R14.2, U9.3, U10.131
/CPU/RS485_RXD: R13.2, U9.1, U10.133
/CPU/RS485_TXD: U9.4, U10.136
/CPU/TCK: J4.4, U6.18, U10.50
/CPU/TDI: J4.8, U6.16, U10.51
/CPU/TDO: J4.6, U6.15, U10.52
/CPU/TEC_COL0: P1.39, U10.115
/CPU/TEC_COL1: P1.31, U10.116
/CPU/TEC_COL2: P1.34, U10.117
/CPU/TEC_F0: P1.33, U10.86
/CPU/TEC_F1: P1.36, U10.85
/CPU/TEC_F2: P1.37, U10.83
/CPU/TEC_F3: P1.35, U10.84
/CPU/TMS: J4.2, U6.14, U10.53
/CPU/USB_DM: T1.3, U2.2, U10.20
/CPU/USB_DP: T1.2, U2.3, U10.19
/CPU/USB_ID: D1.2, J1.4, U10.123
/CPU/USB_JTAG_UART_RXD: U5.38, U10.12
/CPU/USB_JTAG_UART_TXD: U5.39, U10.11
/CPU/VBAT: C6.1, D6.3, U10.42
/CPU/VREFH: C45.1, C47.2, L9.1, U10.32
/CPU/VREFL: C44.2, C45.2, C47.1, L10.1, U10.33
/CPU/WAKEUP: P1.6, U10.120
/Fuente/USB_VBUS: C2.1, C3.1, D3.2, L1.1, U1.6, U1.8, U2.4, U10.22
/GPIO/ADC0_1: R47.1, U10.78
/GPIO/ADC0_2: R46.1, U10.79
/GPIO/ADC0_3: R45.1, U10.80
/GPIO/DAC: R48.1, U10.38
/GPIO/ENET_CRS_DV: P2.10, U10.66
/GPIO/ENET_MDC: P2.8, U10.82
/GPIO/ENET_MDIO: P2.12, U10.81
/GPIO/ENET_REF_CLK: P2.15, U10.72
/GPIO/ENET_RXD0: P2.9, U10.65
/GPIO/ENET_RXD1: P2.4, U10.64
/GPIO/ENET_TXD0: P2.14, U10.68
/GPIO/ENET_TXD1: P2.16, U10.69
/GPIO/ENET_TX_EN: P2.6, U10.67
/GPIO/GPIO0: P2.29, U10.126
/GPIO/GPIO1: P2.32, U10.4
/GPIO/GPIO2: P2.31, U10.2
/GPIO/GPIO3: P2.34, U10.1
/GPIO/GPIO4: P2.33, U10.8
/GPIO/GPIO5: P2.36, U10.7
/GPIO/GPIO6: P2.35, U10.3
/GPIO/GPIO7: P2.38, U10.73
/GPIO/GPIO8: P2.40, U10.55
/GPIO/LCD1: P2.30, U10.141
/GPIO/LCD2: P2.28, U10.142
/GPIO/LCD3: P2.26, U10.143
/GPIO/LCD4: P2.22, U10.144
/GPIO/LCD_EN: P2.23, U10.139
/GPIO/LCD_RS: P2.24, U10.140
/JTAG/CHS_DBG: J3.6, J3.7, J3.8, J3.9, L7.2, U7.1
/JTAG/EECLK: R9.2, U5.62, U8.2
/JTAG/EECS: R8.2, U5.63, U8.1
/JTAG/EEDATA: R11.1, U5.61, U8.3
/JTAG/FT_OE: R7.1, U5.28, U6.1
/JTAG/FT_RST: U5.27, U6.8
/JTAG/FT_TCK: U5.16, U6.2
/JTAG/FT_TDI: U5.17, U6.4
/JTAG/FT_TDO: U5.18, U6.5
/JTAG/FT_TMS: U5.19, U6.6
/JTAG/USB_DEBUG_VBUS: C24.1, C25.1, D4.2, L8.2
/JTAG/USB_JTAG_DM: T2.3, U5.7, U7.3
/JTAG/USB_JTAG_DP: T2.2, U5.8, U7.2
/USB OTG/CHS_OTG: D1.1, J1.6, J1.7, J1.8, J1.9, L2.2, U2.1
/USB OTG/USB0_PPWR: R1.2, U1.1, U10.125
/USB OTG/USB0_PWR_FAULT: R2.2, U1.2, U10.124
/USB OTG/USB_DM_OTG: J1.2, T1.4
/USB OTG/USB_DP_OTG: J1.3, T1.1
GND: BT1.2, C1.2, C2.2, C3.2, C4.2, C5.2, C6.2, C7.2, C8.2, C9.2, C10.2, C11.2, C12.2, C13.2, C14.2, C15.2, C16.2, C17.2, C18.2, C19.2, C20.2, C21.2, C22.2, C23.2, C24.2, C25.2, C26.2, C27.1, C28.2, C29.2, C30.2, C31.2, C33.2, C34.2, C35.2, C37.2, C38.2, C39.2, C40.2, C41.2, C42.2, C43.2, C46.2, C48.1, C49.2, C52.2, C53.2, D5.2, D7.2, D9.2, D13.2, D14.2, D16.1, J1.5, J2.1, J3.5, J4.3, J4.5, J4.9, L2.1, L4.1, L7.1, MH1.1, MH2.1, MH3.1, MH4.1, P1.4, P1.20, P1.22, P1.24, P1.26, P1.28, P1.30, P1.32, P1.38, P1.40, P2.3, P2.5, P2.7, P2.11, P2.13, P2.17, P2.19, P2.25, P2.27, P2.37, P2.39, Q1.S, Q2.S, Q3.S, Q4.S, Q5.S, Q6.S, R1.1, R4.1, R12.1, R14.1, R17.2, R18.2, R27.2, R30.2, R31.2, R36.2, R39.2, R40.2, S5.3, S5.4, SW1.3, SW1.4, SW2.3, SW2.4, SW3.3, SW3.4, SW4.3, SW4.4, TP1.2, TP2.2, TP3.1, U1.3, U3.1, U5.1, U5.5, U5.10, U5.11, U5.13, U5.15, U5.25, U5.35, U5.47, U5.51, U6.10, U6.11, U6.13, U6.17, U6.19, U8.5, U9.5, U10.6, U10.17, U10.18, U10.44, U10.57, U10.71, U10.93, U10.107, U10.121, U10.134, Y1.2, Y1.4, Y2.2, Y2.4, Y3.2, Y3.4
GNDA: C50.2, C51.1, L4.2, L10.2, P1.7, P1.8, P1.10, P1.12, P1.14, P1.16, P1.18, U10.34
unnamed: BT1.1, D6.1
unnamed: C8.1, U5.2, Y3.3
unnamed: C11.1, C13.1, L6.2, U5.4
unnamed: C12.1, C14.1, L5.2, U5.9
unnamed: C28.1, R19.2, R23.2, SW1.1, SW1.2
unnamed: C29.1, R20.2, R24.2, SW2.1, SW2.2
unnamed: C30.1, R21.2, R25.2, SW3.1, SW3.2
unnamed: C31.1, R22.2, R26.2, SW4.1, SW4.2
unnamed: C44.1, U10.37
unnamed: C46.1, U10.21
unnamed: C48.2, D15.1, R55.2, S5.1, S5.2, U10.74
unnamed: C49.1, R54.1, U10.46, Y2.3
unnamed: C52.1, R54.2, U10.45, Y2.1
unnamed: C53.1, U5.3, Y3.1
unnamed: D2.2, J2.2
unnamed: D5.1, R3.2
unnamed: D7.1, D8.1, F1.1, JP2.2, JP3.2, U9.6
unnamed: D8.2, D9.1, F2.1, JP4.2, R16.2, U9.7
unnamed: D10.2, R43.1
unnamed: D11.2, R35.1
unnamed: D12.2, R44.1
unnamed: D13.1, R49.1
unnamed: D14.1, R51.1
unnamed: F1.2, J5.1
unnamed: F2.2, J5.2
unnamed: F3.1, P1.1
unnamed: F4.1, P1.2
unnamed: F5.1, P2.1
unnamed: F6.1, P2.2
unnamed: J1.1, L1.2
unnamed: J3.1, L8.1, U7.4
unnamed: J3.2, T2.4
unnamed: J3.3, T2.1
unnamed: J5.3, R18.1
unnamed: JP1.1, R12.2, U9.2
unnamed: JP2.1, R15.2
unnamed: JP3.1, R16.1
unnamed: JP4.1, R17.1
unnamed: LED1.1, R29.1
unnamed: LED1.2, R38.1
unnamed: LED1.3, R34.1
unnamed: P1.9, R45.2
unnamed: P1.11, R46.2
unnamed: P1.13, R47.2
unnamed: P1.15, R48.2
unnamed: Q1.D, R29.2
unnamed: Q1.G, R28.2
unnamed: Q2.D, R34.2
unnamed: Q2.G, R32.2
unnamed: Q3.D, R35.2
unnamed: Q3.G, R33.2
unnamed: Q4.D, R38.2
unnamed: Q4.G, R37.2
unnamed: Q5.D, R43.2
unnamed: Q5.G, R41.2
unnamed: Q6.D, R44.2
unnamed: Q6.G, R42.2
unnamed: R4.2, U5.6
unnamed: R5.2, U5.14
unnamed: R6.2, U10.54
unnamed: R10.2, R11.2, U8.4
unnamed: R49.2, U10.58
unnamed: R51.2, U10.59
unnamed: U10.40, Y1.1
unnamed: U10.41, Y1.3
